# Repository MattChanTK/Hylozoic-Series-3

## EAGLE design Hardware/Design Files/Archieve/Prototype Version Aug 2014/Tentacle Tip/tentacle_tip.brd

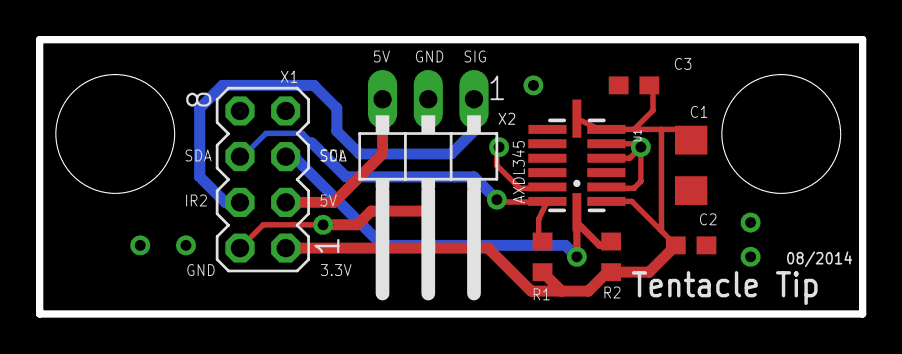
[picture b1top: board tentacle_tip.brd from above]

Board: 2 copper layers, 45.7 x 15.2 mm, 8 parts (0 on the bottom side), 6 nets.

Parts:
C1: 10uF; C1206
C2, C3: 0.1uF; C0603
R1, R2: 2.2k; R0603
U1: ADXL345; LGA14_LONG
X1: MA04-2
X2: 1X03/90

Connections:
+3.3V: C1.1, C2.1, C3.1, R1.2, R2.2, U1.1, U1.6, U1.7, X1.1
+5V: X1.3, X2.3
GND: C1.2, C2.2, C3.2, U1.2, U1.4, U1.5, U1.12, X1.2, X2.2
IR2: X1.4, X2.1
SCL: R2.1, U1.14, X1.5
SDA: R1.1, U1.13, X1.6

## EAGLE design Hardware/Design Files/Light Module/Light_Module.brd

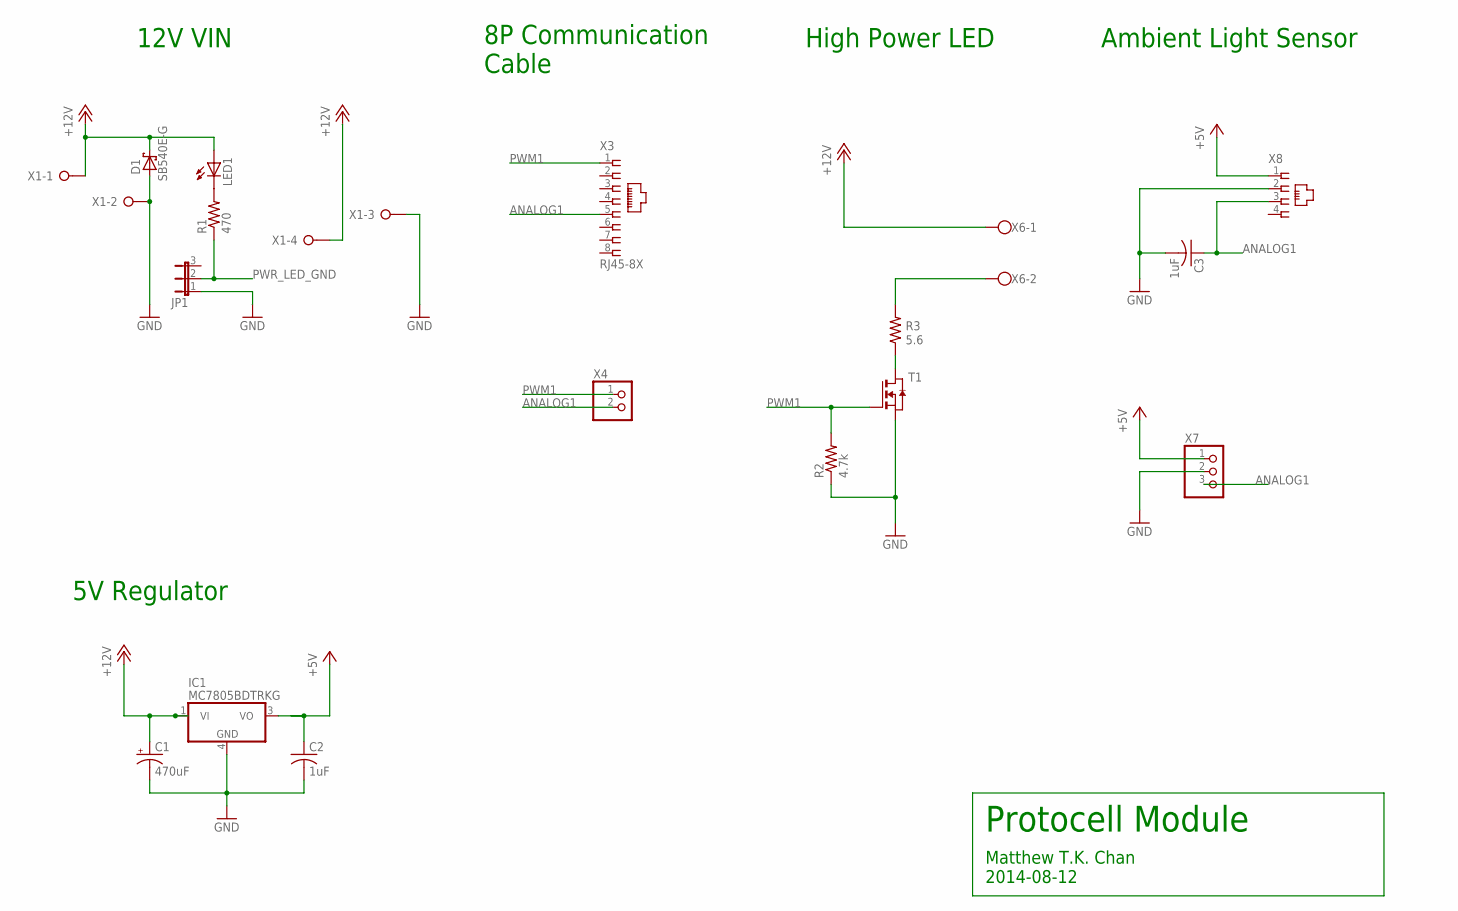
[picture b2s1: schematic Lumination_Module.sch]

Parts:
C1: 470uF; E5-10,5
C2, C3: 1uF; C0603
D1: SB540E-G; DO201T15
IC1: MC7805BDTRKG; DPACK_3
JP1: JP2E; JP2
LED1: LEDSML1206; SML1206
R1: 470; R0603
R2: 4.7k; R0603
R3: 5.6; YAGEO_SQP500JB
T1: NTD5867NLT4G; DPACK
X1: W237-04P; W237-4P
X3: RJ45-8X; RJ45-NO-SHIELD
X4: PINHD-1X2; 1X02
X6: W237-102
X7: PINHD-1X3; 1X03
X8: 558872-1

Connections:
+5V: C2.1, IC1.3 (VO), X7.1, X8.1
+12V: C1.+, D1.C, IC1.1 (VI), LED1.A, X1.1, X1.4, X6.1
ANALOG1: C3.1, X3.5, X4.2, X7.3, X8.3
GND: C1.-, C2.2, C3.2, D1.A, IC1.4 (GND), JP1.1, R2.1, T1.3 (S), X1.2, X1.3, X7.2, X8.2
unnamed: R3.1, T1.2 (D)
unnamed: R3.2, X6.2
unnamed: LED1.C, R1.2
PWM1: R2.2, T1.1 (G), X3.1, X4.1
PWR_LED_GND: JP1.2, R1.1

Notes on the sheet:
Protocell Module
Matthew T.K. Chan 2014-08-12
High Power LED
Ambient Light Sensor
12V VIN
5V Regulator
8P Communication Cable

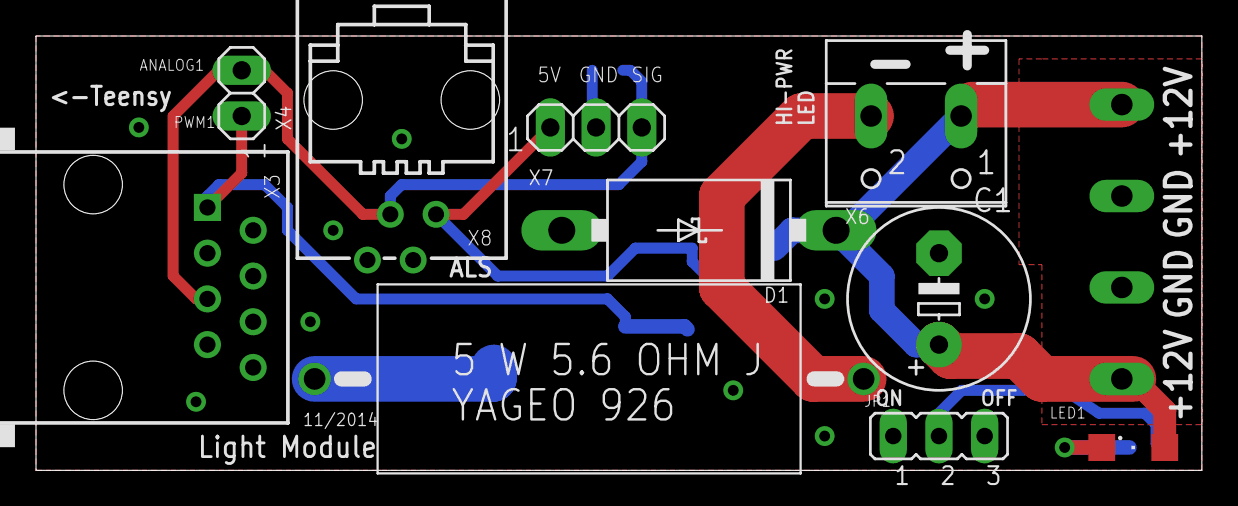
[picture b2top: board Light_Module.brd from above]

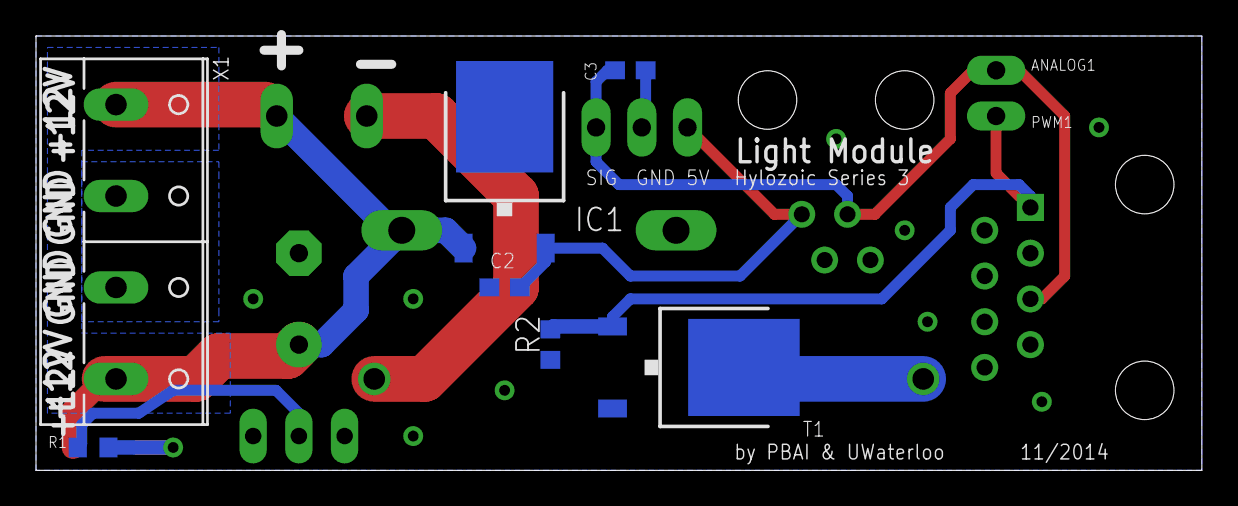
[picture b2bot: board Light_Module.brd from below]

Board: 2 copper layers, 64.8 x 24.1 mm, 17 parts (7 on the bottom side), 9 nets.

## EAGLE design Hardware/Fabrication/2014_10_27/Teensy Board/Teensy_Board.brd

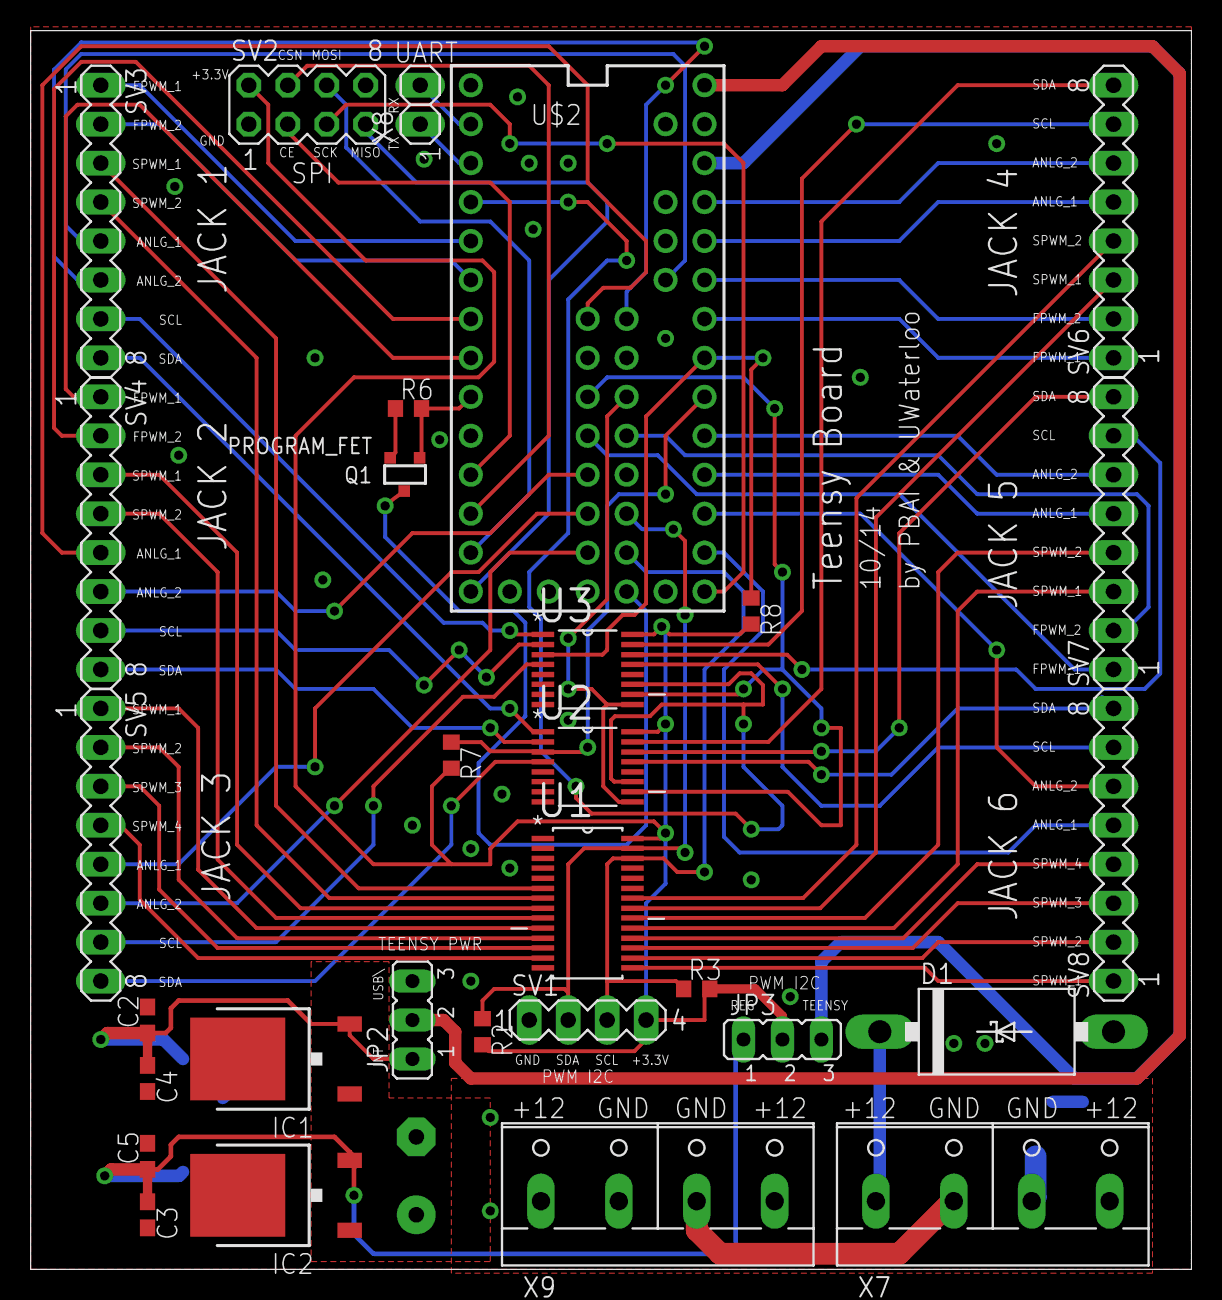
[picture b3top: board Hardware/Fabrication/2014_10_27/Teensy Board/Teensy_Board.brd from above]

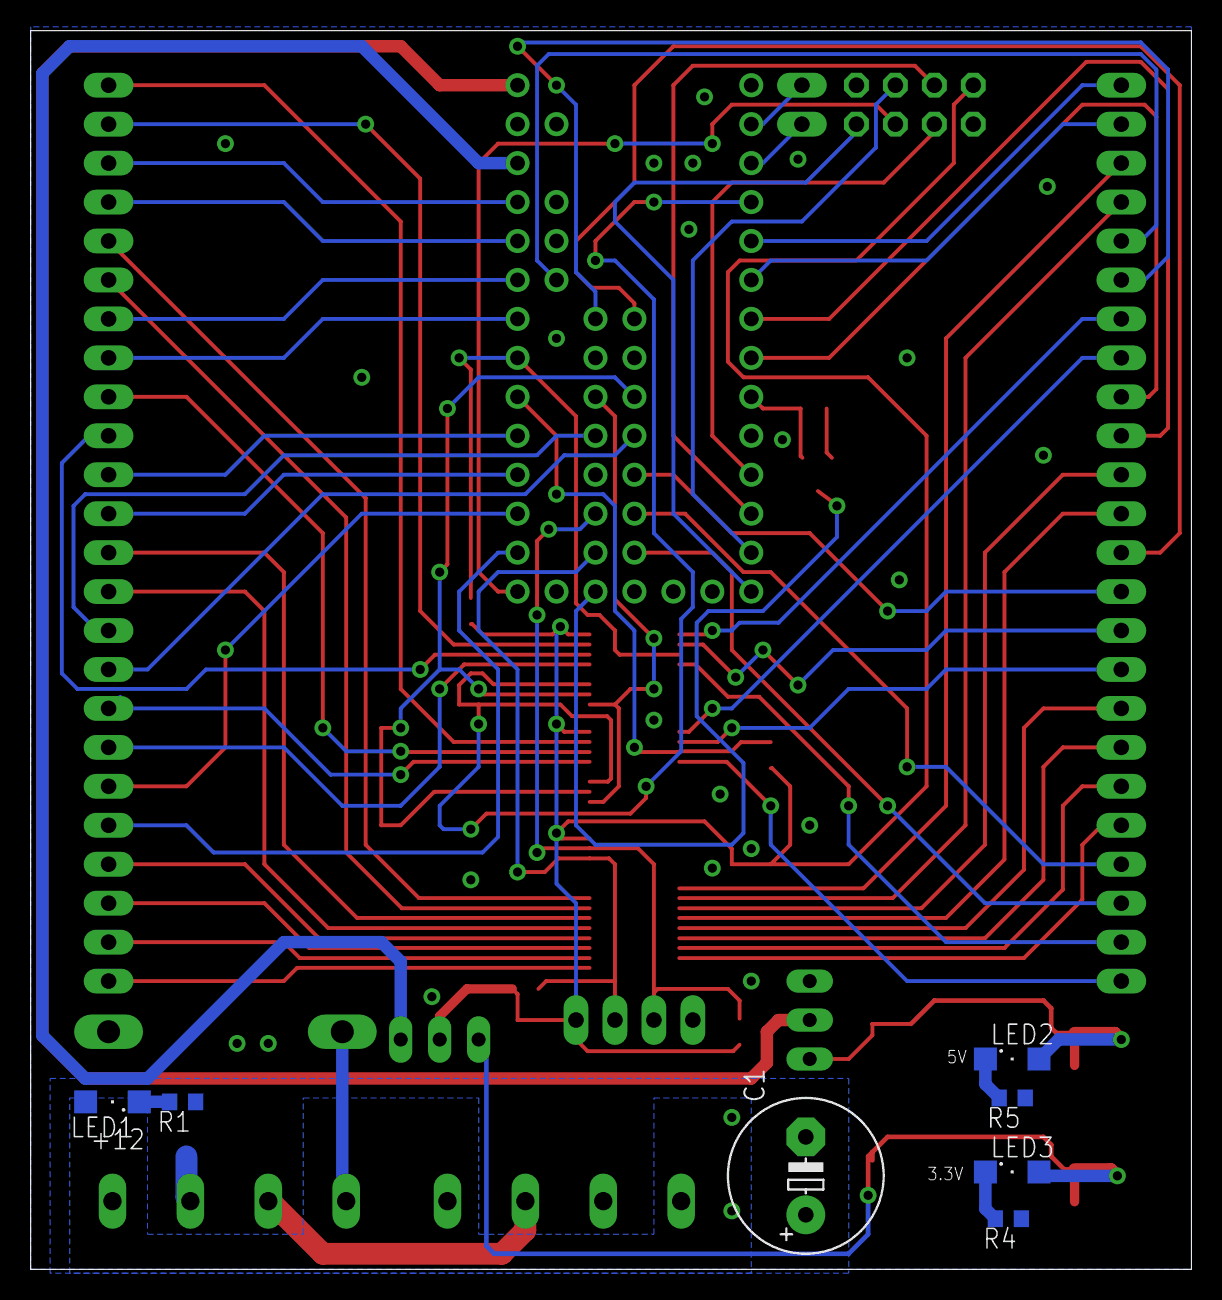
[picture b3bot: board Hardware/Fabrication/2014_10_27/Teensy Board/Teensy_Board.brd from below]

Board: 2 copper layers, 75.7 x 80.8 mm, 37 parts (7 on the bottom side), 74 nets.

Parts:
C1: 470uF; E5-10,5
C2, C3: 1uF; C0603
C4, C5: 100nF; C0603
D1: SB540E-G; DO201T15
IC1: MC7805BDTRKG; DPACK_3
IC2: UA78M33CKVU; DPACK
JP2, JP3: JP2
LED1, LED2, LED3: SML1206
Q1: PROGRAM_FET; SOT-23
R1, R4, R5: 470; R0603
R2, R3, R6: 4k7; R0603
R7, R8: 2.2k; R0603
SV1: PWM_I2C; MA04-1
SV2: SPI; MA04-2
SV3, SV4, SV5, SV6, SV7, SV8: MA08-1
U1: PCA9685PW; SOP65P640X110-28N
U2, U3: 74HC4051PW,118; SOP65P640X110-16N
U$2: TEENSY_3.1_ALL_PINS_AND_PADS; TEENSY_3.1_ALLPINS
X7, X9: W237-4P
X8: UART; 1X02

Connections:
3V3INT: JP3.2, R2.2, R3.2, R7.2, R8.2, SV1.4, SV2.2, U1.28, U2.16, U3.16
+3V3: C3.1, C5.1, IC2.3, JP3.1, LED3.A
+5V: C2.1, C4.1, IC1.3, JP2.1, LED2.A
+12V: C1.+, D1.C, IC1.1, IC2.1, LED1.A, X7.1, X7.4, X9.1, X9.4
A0: SV8.5, U$2.14/A0
A1: SV8.6, U$2.15/A1
A2: SV7.5, U$2.16/A2
A3: SV7.6, U$2.17/A3
A8: SV6.5, U$2.22/A8
A9: SV6.6, U$2.23/A9
A11: SV3.5, U$2.A11
A12: SV4.5, U$2.A12
A13: SV3.6, U$2.A13
A15: SV4.6, U$2.26
A16: SV5.5, U$2.27
A17: SV5.6, U$2.28
CE: SV2.3, U$2.9
CSN: SV2.4, U$2.10
FPWM_1_1: SV3.1, U$2.3
FPWM_1_2: SV3.2, U$2.4
FPWM_2_1: SV4.1, U$2.6
FPWM_2_2: SV4.2, U$2.5
FPWM_4_1: SV6.1, U$2.20/A6
FPWM_4_2: SV6.2, U$2.21/A7
FPWM_5_1: SV7.1, U$2.25
FPWM_5_2: SV7.2, U$2.32
GND: C1.-, C2.2, C3.2, C4.2, C5.2, D1.A, IC1.4, IC2.2, Q1.2, R1.1, R4.1, R5.1, R6.1, SV1.1, SV2.1, U1.1, U1.2, U1.3, U1.4, U1.5, U1.14, U1.23, U1.24, U1.25, U2.6, U2.7, U2.8, U3.6, U3.7, U3.8, U$2.GND, U$2.GND1, U$2.GND2, X7.2, X7.3, X9.2, X9.3
MISO: SV2.7, U$2.12
MOSI: SV2.6, U$2.11
MUL_ADR_0: U2.11, U3.11, U$2.2
MUL_ADR_1: U2.10, U3.10, U$2.24
MUL_ADR_2: U2.9, U3.9, U$2.33
MUL_SCL: R8.1, U3.3, U$2.19/A5
MUL_SCL_1: SV3.7, U3.1
MUL_SCL_2: SV4.7, U3.2
MUL_SCL_3: SV5.7, U3.4
MUL_SCL_4: SV6.7, U3.15
MUL_SCL_5: SV7.7, U3.14
MUL_SCL_6: SV8.7, U3.13
MUL_SDA: R7.1, U2.3, U$2.18/A4
MUL_SDA_1: SV3.8, U2.1
MUL_SDA_2: SV4.8, U2.2
MUL_SDA_3: SV5.8, U2.4
MUL_SDA_4: SV6.8, U2.15
MUL_SDA_5: SV7.8, U2.14
MUL_SDA_6: SV8.8, U2.13
unnamed: LED1.C, R1.2
unnamed: LED3.C, R4.2
unnamed: LED2.C, R5.2
PGM: Q1.3, U$2.PGM
PGM_DO: Q1.1, R6.2, U$2.7
RX1: U$2.0, X8.2
SCK: SV2.5, U$2.13
SCL_PWM: R3.1, SV1.3, U1.26, U$2.29
SDA_PWM: R2.1, SV1.2, U1.27, U$2.30
SPWM_1_1: SV3.3, U1.6
SPWM_1_2: SV3.4, U1.7
SPWM_2_1: SV4.3, U1.8
SPWM_2_2: SV4.4, U1.9
SPWM_3_1: SV5.1, U1.10
SPWM_3_2: SV5.2, U1.11
SPWM_3_3: SV5.3, U1.12
SPWM_3_4: SV5.4, U1.13
SPWM_4_1: SV6.3, U1.21
SPWM_4_2: SV6.4, U1.22
SPWM_5_1: SV7.3, U1.19
SPWM_5_2: SV7.4, U1.20
SPWM_6_1: SV8.1, U1.15
SPWM_6_2: SV8.2, U1.16
SPWM_6_3: SV8.3, U1.17
SPWM_6_4: SV8.4, U1.18
TEENSY_3V3: JP3.3, U$2.3.3V, U$2.3.3V1, U$2.3.3V2
TEENSY_VIN: JP2.2, U$2.VIN
TX1: U$2.1, X8.1

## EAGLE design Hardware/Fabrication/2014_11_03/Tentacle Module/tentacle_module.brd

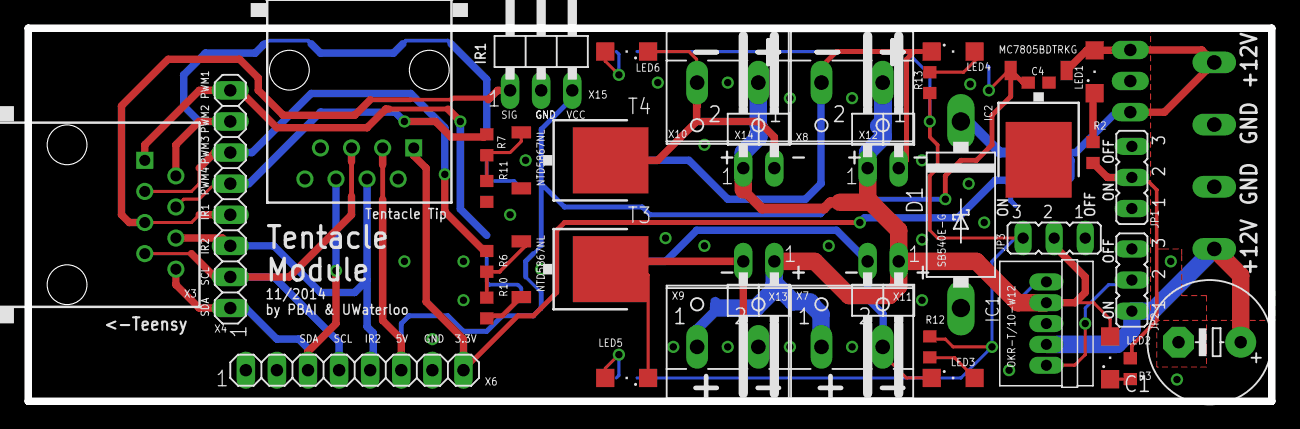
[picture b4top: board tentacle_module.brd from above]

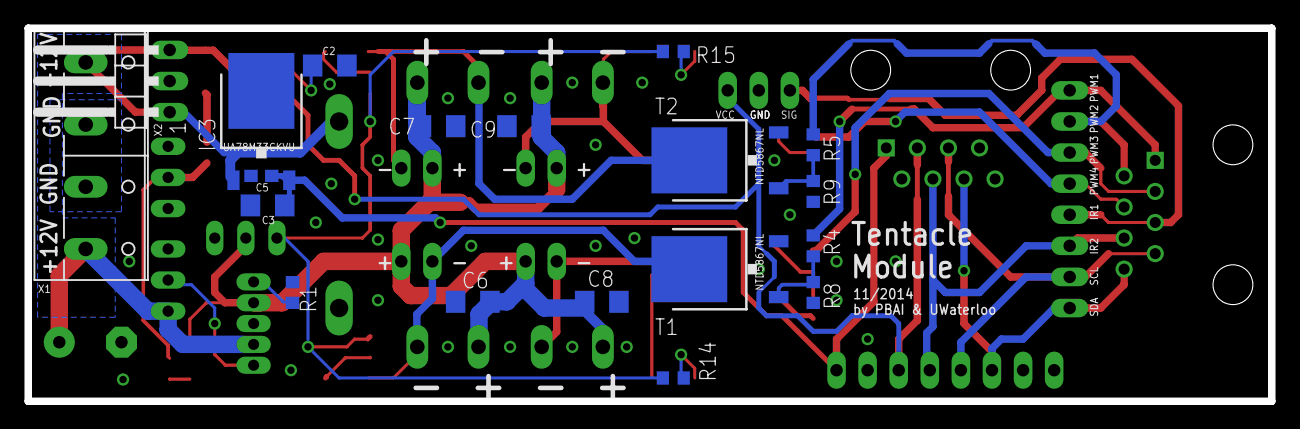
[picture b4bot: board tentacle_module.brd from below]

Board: 2 copper layers, 101.6 x 30.5 mm, 56 parts (19 on the bottom side), 31 nets.

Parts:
C1: 470uF; E5-10,5
C2, C3, C6, C7, C8, C9: 10uF; C1206
C4, C5: 100nF; C0603
D1: SB540E-G; DO201T15
IC1: OKR-T/10-W12; OKR-C90
IC2: MC7805BDTRKG; DPACK_3
IC3: UA78M33CKVU; DPACK
JP1, JP2, JP3: JP2
LED1, LED2, LED3, LED4, LED5, LED6: SML1206
R1: 267; R0603
R2, R3, R12, R13, R14, R15: 470; R0603
R4, R5, R6, R7: 1K; R0603
R8, R9, R10, R11: 4.7K; R0603
T1, T2, T3, T4: NTD5867NL; DPACK
X1: W237-4P
X2, X15: 1X03/90
X3, X5: RJ45-8X; RJ45-NO-SHIELD
X4, X6: 1X08
X7, X8, X9, X10: W237-102
X11, X12, X13, X14: 1X02/90

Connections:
5V_ENABLE: IC1.ON/OFF, JP2.2
+3.3V: C3.1, C5.1, IC3.3, X5.1, X6.8
+5V: C2.1, C4.1, IC2.3, X5.3, X6.6, X15.3
+5V_HI-PWR: C6.1, C7.1, C8.1, C9.1, IC1.VOUT, JP3.2, LED2.A, X7.1, X8.1, X9.1, X10.1, X11.1, X12.1, X13.1, X14.1
+12V: C1.+, D1.C, IC1.VIN, IC2.1, IC3.1, JP2.1, LED1.A, X1.1, X1.4, X2.1, X2.3
GND: C1.-, C2.2, C3.2, C4.2, C5.2, C6.2, C7.2, C8.2, C9.2, D1.A, IC1.GND, IC2.4, IC3.2, JP1.1, JP2.3, R1.1, R8.1, R9.1, R10.1, R11.1, T1.3, T2.3, T3.3, T4.3, X1.2, X1.3, X2.2, X5.2, X6.7, X15.2
IR1: X3.5, X4.4, X15.1
IR2: X3.6, X4.3, X5.4, X6.5
unnamed: R5.2, R9.2, T2.1
unnamed: R6.2, R10.2, T3.1
unnamed: R7.2, R11.2, T4.1
unnamed: R4.2, R8.2, T1.1
unnamed: LED3.A, R12.1
unnamed: IC1.TRIM, R1.2
unnamed: LED2.C, R3.2
unnamed: LED1.C, R2.2
unnamed: LED4.A, R13.1
unnamed: LED5.A, R14.1
unnamed: LED6.A, R15.1
PWM1: R4.1, X3.1, X4.8
PWM2: R5.1, X3.2, X4.7
PWM3: R6.1, X3.3, X4.6
PWM4: R7.1, X3.4, X4.5
PWR_LED_GND: JP1.2, R2.1, R3.1
SCL: X3.7, X4.2, X5.5, X6.4
SDA: X3.8, X4.1, X5.6, X6.3
SMA1_OUT-: LED3.C, T1.2, X7.2, X11.2
SMA2_OUT-: LED4.C, T2.2, X8.2, X12.2
SMA3_OUT-: LED5.C, T3.2, X9.2, X13.2
SMA4_OUT-: LED6.C, T4.2, X10.2, X14.2
TEST_LED_V+: JP3.3, R12.2, R13.2, R14.2, R15.2

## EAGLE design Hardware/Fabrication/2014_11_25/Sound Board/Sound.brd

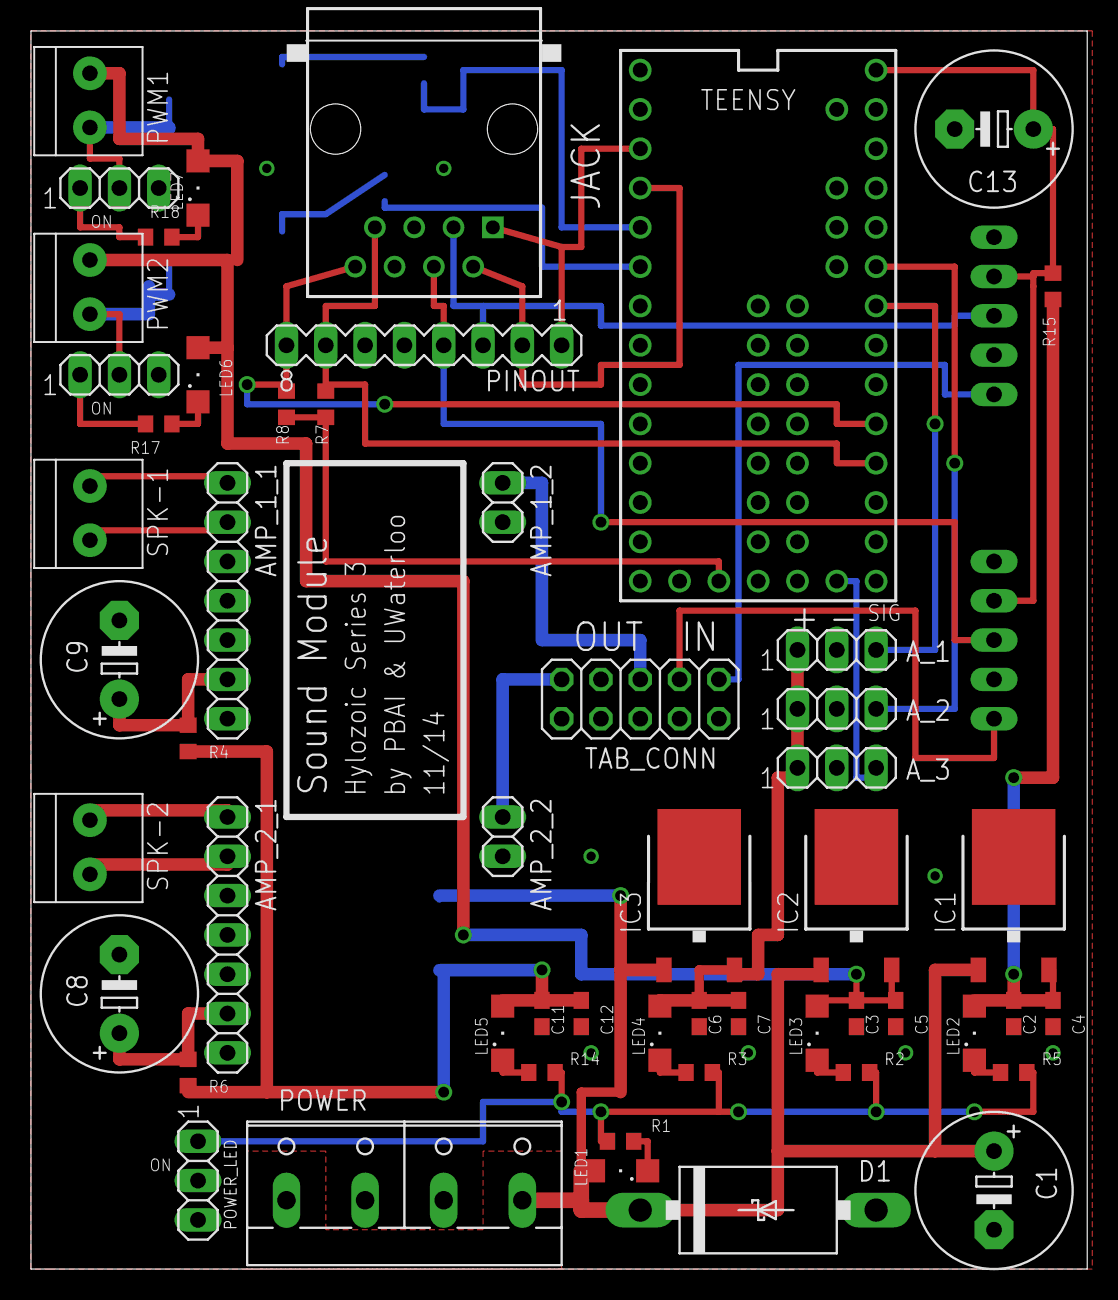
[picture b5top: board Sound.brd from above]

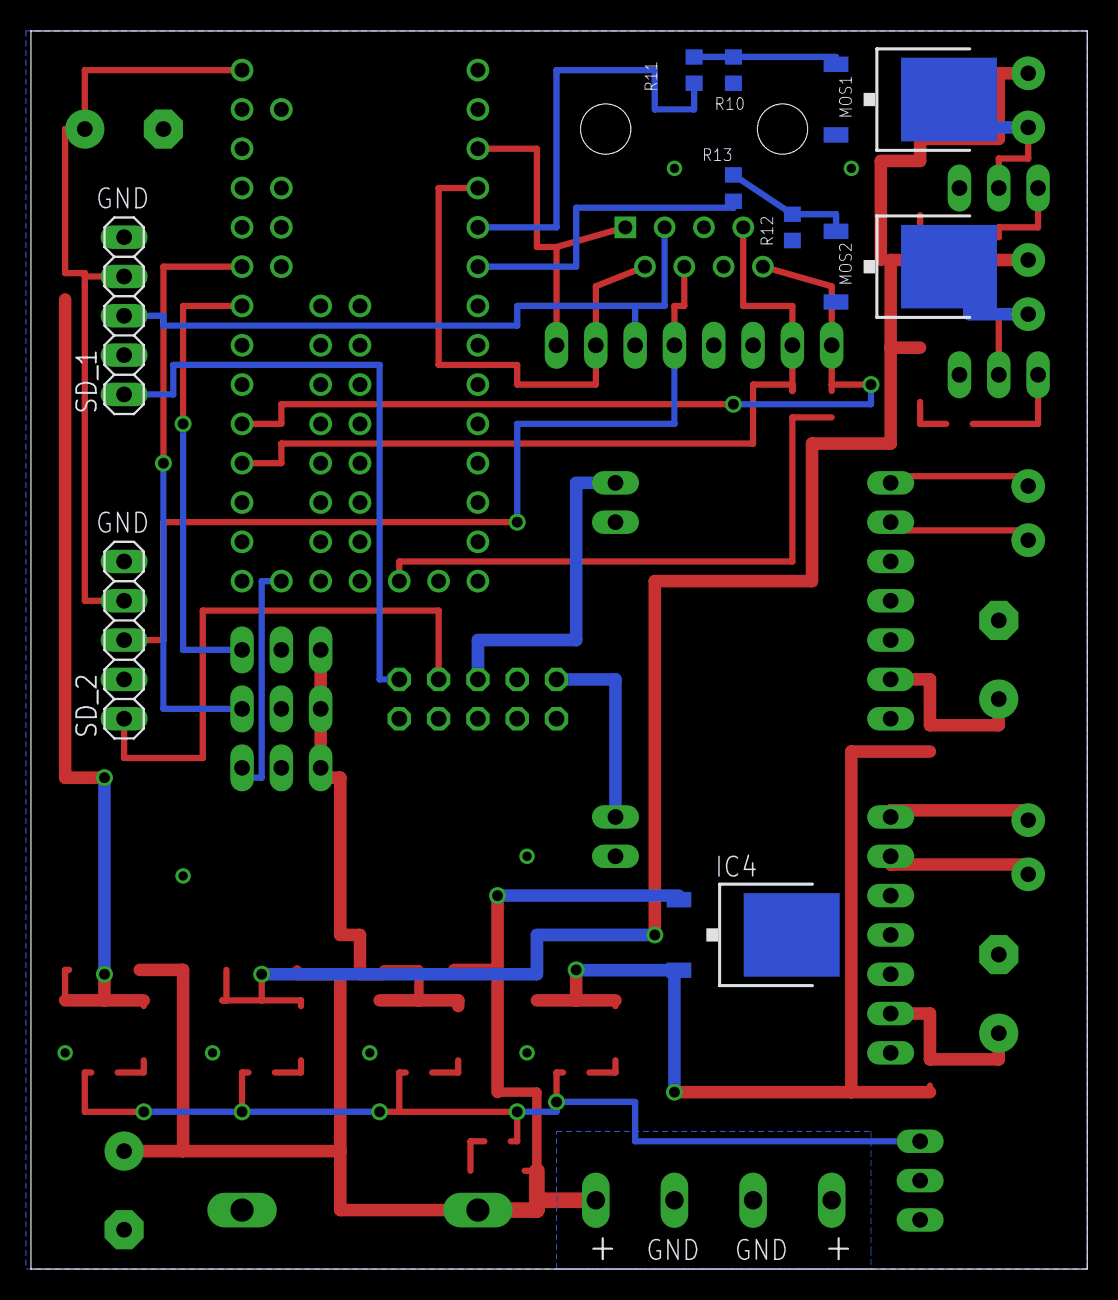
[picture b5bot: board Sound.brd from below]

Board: 2 copper layers, 68.2 x 80.0 mm, 63 parts (9 on the bottom side), 43 nets.

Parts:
AMP_1_1, AMP_2_1: 1X07
AMP_1_2, AMP_2_2: 1X02
A_1, A_2, A_3: 1X03
C1: 2000uF; E5-10,5
C2, C3, C6, C11: 1uF; C0603
C4, C5, C7, C12: 100nF; C0603
C8, C9, C13: 470uF; E5-10,5
D1: SB540E-G; DO201T15
IC1, IC2, IC3, IC4: DPACK_3
JACK: RJ45-6L-B; RJ45-NO-SHIELD
LED1, LED2, LED3, LED4, LED5, LED6, LED7: SML1206
MOS1, MOS2: DPACK
PINOUT: MA08-1
POWER: W237-4P
POWER_LED: 1X03
PWM1, PWM2: 1X2-3.5MM
R1, R2, R3, R5, R14, R17, R18: 470; R0603
R4, R6, R15: 10; R0603
R7, R8: 2.2k; R0603
R10, R12: 4.7K; R0603
R11, R13: 1K; R0603
SD_1, SD_2: 1X05
SPK-1, SPK-2: 1X2-3.5MM
TAB_CONN: 2X05
TEENSY: AUDIO BOARD; TEENSY_3.1_ALLPINS
X2, X3: 1X03

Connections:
3.3V: R7.2, R8.2, TEENSY.3.3V, TEENSY.3.3V1, TEENSY.3.3V2
5VFILT: C13.+, R15.1, SD_1.4, SD_2.4, TEENSY.VIN
+5V_1: C2.1, C4.1, IC1.3, LED2.A, R15.2
+5V_2: C3.1, C5.1, IC2.3, LED3.A, LED6.A, LED7.A, PWM1.2, PWM2.2
+5V_3: A_1.1, A_2.1, A_3.1, C6.1, C7.1, IC3.3, LED4.A
+5V_4: C11.1, C12.1, IC4.3, LED5.A, R4.2, R6.2
+12V: C1.+, D1.C, IC1.1, IC2.1, IC3.1, IC4.1, LED1.A, POWER.1, POWER.4
AMP_1_VIN: AMP_1_1.6, C9.+, R4.1
AMP_2_VIN: AMP_2_1.6, C8.+, R6.1
DPEAK_1: JACK.3, PINOUT.3, SD_1.3
DPEAK_2: JACK.4, PINOUT.4, SD_2.3
DTRIG_1: JACK.1, PINOUT.1, TEENSY.1
DTRIG_2: JACK.2, PINOUT.2, TEENSY.2
FPWM_1_1: R11.2, TEENSY.3
FPWM_1_2: R13.2, TEENSY.4
GND: AMP_1_1.5, AMP_1_2.2, AMP_2_1.5, AMP_2_2.2, A_1.2, A_2.2, A_3.2, C1.-, C2.2, C3.2, C4.2, C5.2, C6.2, C7.2, C8.-, C9.-, C11.2, C12.2, C13.-, D1.A, IC1.4, IC2.4, IC3.4, IC4.4, MOS1.3, MOS2.3, POWER.2, POWER.3, POWER_LED.2, R10.1, R12.1, SD_1.5, SD_2.5, TAB_CONN.2, TAB_CONN.4, TAB_CONN.7, TEENSY.GND, TEENSY.GND1, TEENSY.GND2
IN_1+: AMP_1_2.1, TAB_CONN.5
IN_2+: AMP_2_2.1, TAB_CONN.9
LED_JUMP_POW: POWER_LED.1, R1.1, R2.1, R3.1, R5.1, R14.1
MIC_1: SD_1.1, TAB_CONN.1
MIC_2: SD_2.1, TAB_CONN.3
unnamed: MOS2.1, R12.2, R13.1
unnamed: LED3.C, R2.2
unnamed: LED4.C, R3.2
unnamed: MOS1.1, R10.2, R11.1
unnamed: MOS1.2, PWM1.1, X2.2
unnamed: LED6.C, R17.2
unnamed: MOS2.2, PWM2.1, X3.2
unnamed: LED5.C, R14.2
unnamed: LED7.C, R18.2
unnamed: LED1.C, R1.2
unnamed: R18.1, X2.1
unnamed: R17.1, X3.1
unnamed: LED2.C, R5.2
SCL: JACK.7, PINOUT.7, R7.1, TEENSY.16/A2
SDA: JACK.8, PINOUT.8, R8.1, TEENSY.17/A3
SIG_1: A_1.3, TEENSY.20/A6
SIG_2: A_2.3, TEENSY.21/A7
SIG_3: A_3.3, TEENSY.A14
SPK_1+: AMP_1_1.1, SPK-1.2
SPK_1-: AMP_1_1.2, SPK-1.1
SPK_2+: AMP_2_1.1, SPK-2.2
SPK_2-: AMP_2_1.2, SPK-2.1

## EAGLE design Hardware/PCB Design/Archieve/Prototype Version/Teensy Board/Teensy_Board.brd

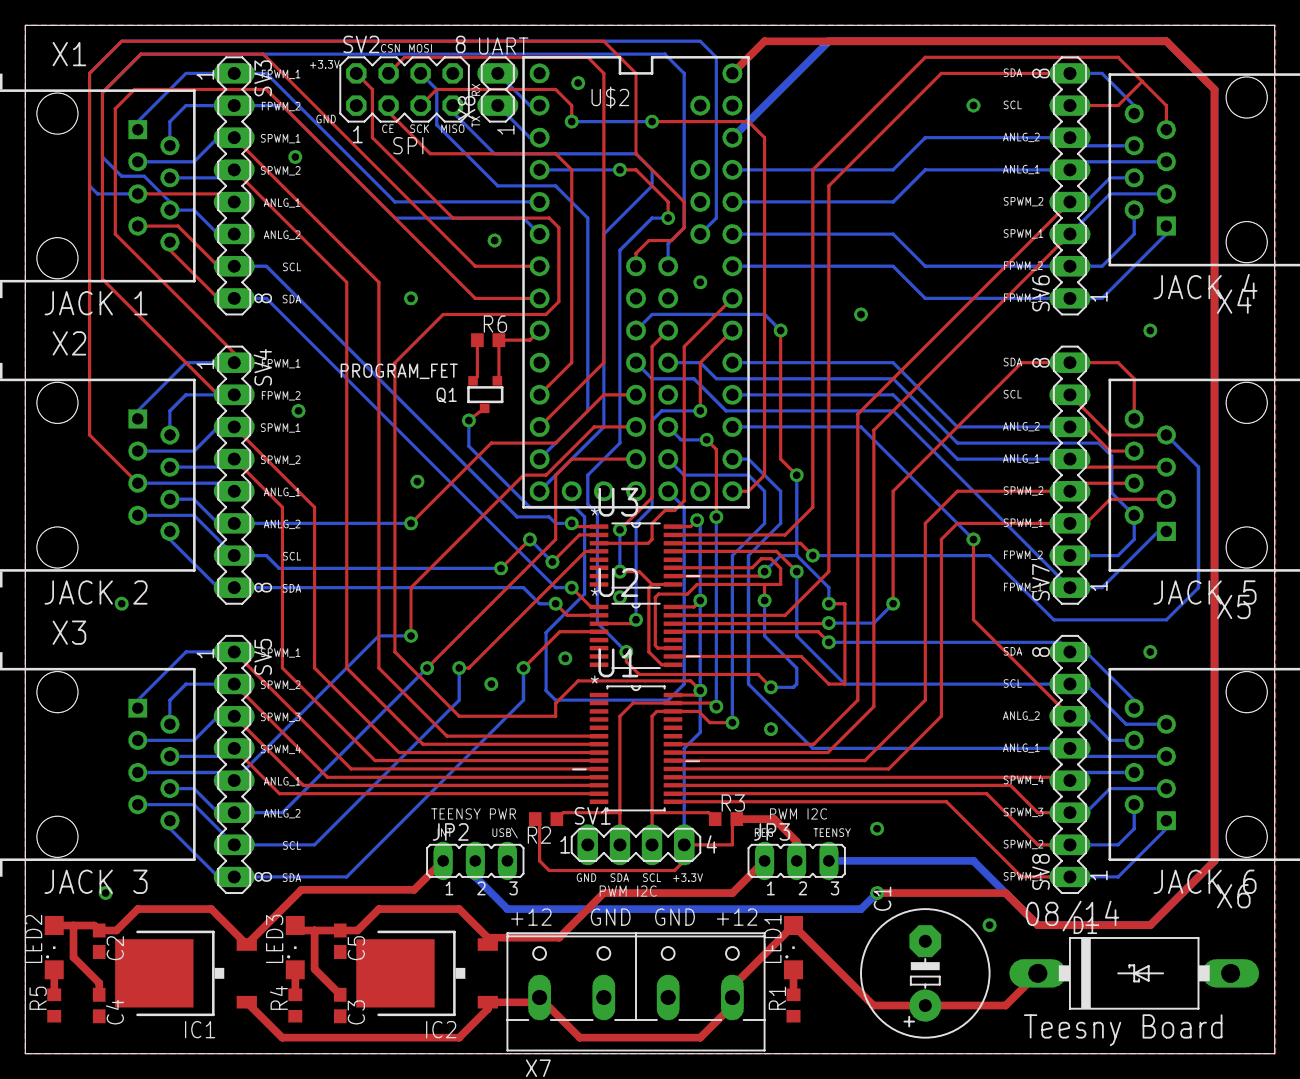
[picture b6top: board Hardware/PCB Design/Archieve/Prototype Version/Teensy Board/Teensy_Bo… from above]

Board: 2 copper layers, 98.7 x 81.3 mm, 40 parts (0 on the bottom side), 74 nets.

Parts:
C1: 470uF; E5-10,5
C2, C3: 1uF; C0603
C4, C5: 100nF; C0603
D1: SB540E-G; DO201T15
IC1: MC7805BDTRKG; DPACK_3
IC2: UA78M33CKVU; DPACK
JP2, JP3: JP2
LED1, LED2, LED3: SML1206
Q1: PROGRAM_FET; SOT-23
R1, R4, R5: 470; R0603
R2, R3, R6: 4k7; R0603
SV1: PWM_I2C; MA04-1
SV2: SPI; MA04-2
SV3, SV4, SV5, SV6, SV7, SV8: MA08-1
U1: PCA9685PW; SOP65P640X110-28N
U2, U3: 74HC4051PW,118; SOP65P640X110-16N
U$2: TEENSY_3.1_ALL_PINS_AND_PADS; TEENSY_3.1_ALLPINS
X1, X2, X3, X4, X5, X6: RJ45-8X; RJ45-NO-SHIELD
X7: W237-4P
X8: UART; 1X02

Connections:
3V3INT: JP3.2, R2.2, R3.2, SV1.4, SV2.2, U1.28, U2.16, U3.16
+3V3: C3.1, C5.1, IC2.3, JP3.1, LED3.A
+5V: C2.1, C4.1, IC1.3, JP2.1, LED2.A
+12V: C1.+, D1.C, IC1.1, IC2.1, LED1.A, X7.1, X7.4
A0: SV8.5, U$2.14/A0, X6.5
A1: SV8.6, U$2.15/A1, X6.6
A2: SV7.5, U$2.16/A2, X5.5
A3: SV7.6, U$2.17/A3, X5.6
A8: SV6.5, U$2.22/A8, X4.5
A9: SV6.6, U$2.23/A9, X4.6
A11: SV3.5, U$2.A11, X1.5
A12: SV4.5, U$2.A12, X2.5
A13: SV3.6, U$2.A13, X1.6
A15: SV4.6, U$2.26, X2.6
A16: SV5.5, U$2.27, X3.5
A17: SV5.6, U$2.28, X3.6
CE: SV2.3, U$2.9
CSN: SV2.4, U$2.10
FPWM_1_1: SV3.1, U$2.3, X1.1
FPWM_1_2: SV3.2, U$2.4, X1.2
FPWM_2_1: SV4.1, U$2.6, X2.1
FPWM_2_2: SV4.2, U$2.5, X2.2
FPWM_4_1: SV6.1, U$2.20/A6, X4.1
FPWM_4_2: SV6.2, U$2.21/A7, X4.2
FPWM_5_1: SV7.1, U$2.25, X5.1
FPWM_5_2: SV7.2, U$2.32, X5.2
GND: C1.-, C2.2, C3.2, C4.2, C5.2, D1.A, IC1.4, IC2.2, Q1.2, R1.1, R4.1, R5.1, R6.1, SV1.1, SV2.1, U1.1, U1.2, U1.3, U1.4, U1.5, U1.14, U1.23, U1.24, U1.25, U2.6, U2.7, U2.8, U3.6, U3.7, U3.8, U$2.GND, U$2.GND1, U$2.GND2, X7.2, X7.3
MISO: SV2.7, U$2.12
MOSI: SV2.6, U$2.11
MUL_ADR_0: U2.11, U3.11, U$2.2
MUL_ADR_1: U2.10, U3.10, U$2.24
MUL_ADR_2: U2.9, U3.9, U$2.33
MUL_SCL: U3.3, U$2.19/A5
MUL_SCL_1: SV3.7, U3.1, X1.7
MUL_SCL_2: SV4.7, U3.2, X2.7
MUL_SCL_3: SV5.7, U3.4, X3.7
MUL_SCL_4: SV6.7, U3.15, X4.7
MUL_SCL_5: SV7.7, U3.14, X5.7
MUL_SCL_6: SV8.7, U3.13, X6.7
MUL_SDA: U2.3, U$2.18/A4
MUL_SDA_1: SV3.8, U2.1, X1.8
MUL_SDA_2: SV4.8, U2.2, X2.8
MUL_SDA_3: SV5.8, U2.4, X3.8
MUL_SDA_4: SV6.8, U2.15, X4.8
MUL_SDA_5: SV7.8, U2.14, X5.8
MUL_SDA_6: SV8.8, U2.13, X6.8
unnamed: LED1.C, R1.2
unnamed: LED3.C, R4.2
unnamed: LED2.C, R5.2
PGM: Q1.3, U$2.PGM
PGM_DO: Q1.1, R6.2, U$2.7
RX1: U$2.0, X8.2
SCK: SV2.5, U$2.13
SCL_PWM: R3.1, SV1.3, U1.26, U$2.29
SDA_PWM: R2.1, SV1.2, U1.27, U$2.30
SPWM_1_1: SV3.3, U1.6, X1.3
SPWM_1_2: SV3.4, U1.7, X1.4
SPWM_2_1: SV4.3, U1.8, X2.3
SPWM_2_2: SV4.4, U1.9, X2.4
SPWM_3_1: SV5.1, U1.10, X3.1
SPWM_3_2: SV5.2, U1.11, X3.2
SPWM_3_3: SV5.3, U1.12, X3.3
SPWM_3_4: SV5.4, U1.13, X3.4
SPWM_4_1: SV6.3, U1.21, X4.3
SPWM_4_2: SV6.4, U1.22, X4.4
SPWM_5_1: SV7.3, U1.19, X5.3
SPWM_5_2: SV7.4, U1.20, X5.4
SPWM_6_1: SV8.1, U1.15, X6.1
SPWM_6_2: SV8.2, U1.16, X6.2
SPWM_6_3: SV8.3, U1.17, X6.3
SPWM_6_4: SV8.4, U1.18, X6.4
TEENSY_3V3: JP3.3, U$2.3.3V, U$2.3.3V1, U$2.3.3V2
TEENSY_VIN: JP2.2, U$2.VIN
TX1: U$2.1, X8.1

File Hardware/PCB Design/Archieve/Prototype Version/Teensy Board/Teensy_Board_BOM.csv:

"Qty";"Value";"Device";"Package";"Parts";"Description";"MF";"MPN";"OC_FARNELL";"OC_NEWARK";"PACKAGE";"SUPPLIER";
"1";"";"2N7002_SOT23";"SOT-23";"Q1";"2N7000, 2N7002, NDS7002A";"";"";"";"";"";"";
"2";"";"JP2E";"JP2";"JP2, JP3";"JUMPER";"";"";"";"";"";"";
"3";"";"LEDSML1206";"SML1206";"LED1, LED2, LED3";"LED";"";"";"";"";"";"";
"1";"";"MA04-1";"MA04-1";"SV1";"PIN HEADER";"";"";"unknown";"unknown";"";"";
"1";"";"MA04-2";"MA04-2";"SV2";"PIN HEADER";"";"";"unknown";"unknown";"";"";
"6";"";"MA08-1";"MA08-1";"SV3, SV4, SV5, SV6, SV7, SV8";"PIN HEADER";"";"";"unknown";"unknown";"";"";
"1";"";"W237-04P";"W237-4P";"X7";"WAGO SREW CLAMP";"";"";"unknown";"unknown";"";"";
"2";"100nF";"C-USC0603";"C0603";"C4, C5";"CAPACITOR, American symbol";"";"";"";"";"";"";
"2";"1uF";"C-USC0603";"C0603";"C2, C3";"CAPACITOR, American symbol";"";"";"";"";"";"";
"3";"470";"R-US_R0603";"R0603";"R1, R4, R5";"RESISTOR, American symbol";"";"";"";"";"";"";
"1";"470uF";"CPOL-USE5-10.5";"E5-10,5";"C1";"POLARIZED CAPACITOR, American symbol";"";"";"";"";"";"";
"3";"4k7";"R-US_R0603";"R0603";"R2, R3, R6";"RESISTOR, American symbol";"";"";"";"";"";"";
"2";"74HC4051PW,118";"74HC4051PW,118";"SOP65P640X110-16N";"U2, U3";"8-channel analog multiplexer/demultiplexer";"";"74HC4051PW,118";"1826843";"78R6260";"TSSOP-16";"NXP";
"1";"MC7805BDTRKG";"MC7805BDTRKG";"DPACK_3";"IC1";"1A Positive Voltage Regulators";"";"";"";"";"";"";
"1";"PCA9685PW";"PCA9685PW";"SOP65P640X110-28N";"U1";"16-channel, 12-bit PWM Fm+ I2C-bus LED controller";"";"PCA9685PW";"1854074";"19T6398";"TSSOP-28";"NXP";
"6";"RJ45-8X";"RJ45-8X";"RJ45-NO-SHIELD";"X1, X2, X3, X4, X5, X6";"CORCOM Modular RJ Jacks No Shield";"";"RJ45-8X";"unknown";"16R6101";"";"";
"1";"SB540E-G";"SB540E-G";"DO201T15";"D1";"SCHOTTKY BARRIER RECTIFIER 3.0 AMPERES 20, 30, 40 VOLT";"";"";"";"";"";"";
"1";"TEENSY_3.1_ALL_PINS_AND_PADS";"TEENSY_3.1_ALL_PINS_AND_PADS";"TEENSY_3.1_ALLPINS";"U$2";"Footprint for Teensy 3.1 board using all pads and all through-holes. Pads need a 2x7 0.1" SMD header.";"";"";"";"";"";"";
"1";"UA78M33CKVU";"UA78M33CKVU";"DPACK";"IC2";"Linear Voltage Reg";"";"";"";"";"";"";
